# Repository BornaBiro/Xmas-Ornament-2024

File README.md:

# Xmas Ornament - 2024 update
New and updated DIY Xmas Ornament based around STM32C011 MCU.

# ! NOTE ! - PLEASE READ THIS FIRST!
Before making this project keep in mind that this PCB has an error. It's not fixed in design files, you will need it to fix it yourself!

Issues is that STM32 MCU is missing it's GND.

The fix is to scratch the soldermask and connect GND of the MCU with a piece of very thin wire.

## Board features
- Low power STM32C011F6PF MCU with 48MHz internal clock
- 12 x WS2812B-2020 RGB Adressable LEDs
- Buzzer for playing simple melodies
- Two push buttons both with wake up capability
- JST battry connector
- Li-Ion battery charger
- Low power compatable - 2uA deep sleep current
- USB-C connector for charging

I made two version of the project: one with the flex PCB (ordered from JLCPCB) and the other one with regular two layer FR4 PCB.

Flex PCB version:

FR4 PCB version:

## Board usage:
There are two buttons for controlling the ornament. At moment of connecting the battery, device is on and it's playing the melodies and also blinking the LEDs. Battery used is Li-Ion 3.7V 601220 100mAh Battery. Please check the polarity of. the battery!

- BTN1:
  - Regular button press:
    - Power on if the device is off
    - Change the melody
  - Multiple press: Noting for now. :)
  - Long press: Power down

- BTN2:
  - Regular button press: Change the LED pattern
  - Multiple press: Noting for now. :)
  - Long press: Mute/Unmute the ornament

## Requirements
- PC or a laptop
- STM32CubeIDE v1.19.0 or older (yes, older, new v2.0.0 is just bad)
  - I used STM32CubeIDE v1.19.0, Build: 25607_20250703_0907 (UTC)
- STM32C0 FW package v1.4.0
- STLink v2 (ideally with [reset mod](https://chauquest.com/index.php/article/why-your-st-link-v2-reset-doesnt-work-and-how-to-fix-it/))
- Completed PCB
- Jumper cables to connect STLink and PCB
- Soldering iron
- Li-Ion battery
- Electricity for all of that (not optional!)

## Usage
Open the project in STM32CubeIDE, build it (everything should be set-up) by pressing CTRL+B (or CMD+B on Mac) , and run the code. If, on the code run (upload) pop-up window shows up, just press Run button and the code should be uploaded to the board. If not, maybe something ins't soldered correctly, or there is a connection issue with the board or the programmer. To check that, you can use STM32CubeProgrammer - it's faster for testing programmer connection than STM32CubeIDE.

# License
All files written or created by me are using the MIT Licence and can be re-used BUT original author (me) must not be removed!
Part of the code for WS2812 LED Driver (ws2182_hsv() function code) is copied from the [Adafruit_NeoPixel library](https://github.com/adafruit/Adafruit_NeoPixel). Thanks Adafruit!

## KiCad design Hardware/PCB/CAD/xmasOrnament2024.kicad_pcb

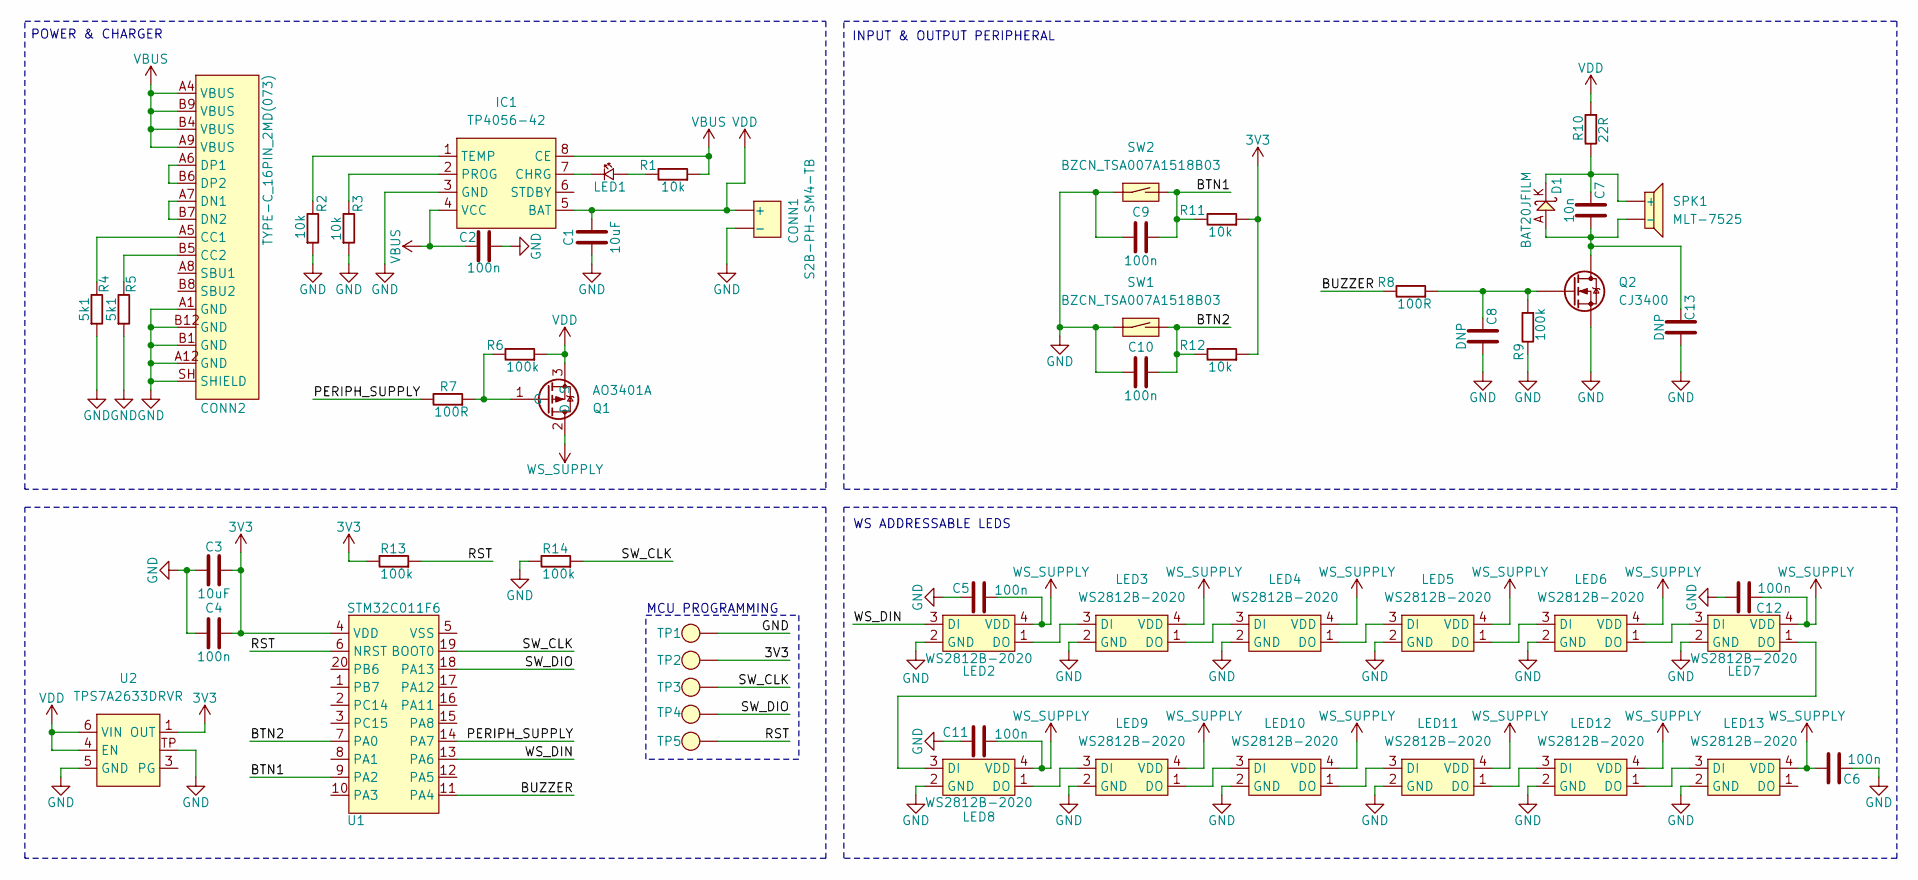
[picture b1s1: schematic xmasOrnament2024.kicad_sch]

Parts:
C1, C3: 10uF; C1206
C2, C4, C5, C6, C9, C10, C11, C12: 100n; C0603
C7: 10n; C0603
C8, C13: DNP; C0603
CONN1: S2B-PH-SM4-TB; JST_S2B-PH-SM4-TB
CONN2: TYPE-C_16PIN_2MD(073)
D1: BAT20JFILM; SOD323
IC1: TP4056-42; EMSOP
LED1: LED_0603
LED2, LED3, LED4, LED5, LED6, LED7, LED8, LED9, LED10, LED11, LED12, LED13: WS2812B-2020
Q1: AO3401A; SOT-23-3L
Q2: CJ3400; SOT-23-3L
R1, R2, R3, R11, R12: 10k; R0603
R4, R5: 5k1; R0603
R6, R9, R13, R14: 100k; R0603
R7, R8: 100R; R0603
R10: 22R; R0603
SPK1: MLT-7525; MTL-7525
SW1, SW2: BZCN_TSA007A1518B03; TSA007A1518B03
TP1, TP2, TP3, TP4, TP5: TP-1_5mm
U1: STM32C011F6; TSSOP20
U2: TPS7A2633DRVR; WSON-6

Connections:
3V3: C3.2, C4.2, R11.1, R12.1, R13.2, TP2.1 (TP), U1.4 (VDD), U2.1 (OUT)
/BTN1: C9.2, R11.2, SW2.2 (SW2), U1.9 (PA2)
/BTN2: C10.2, R12.2, SW1.2 (SW2), U1.7 (PA0)
/BUZZER: R8.2, U1.11 (PA4)
/PERIPH_SUPPLY: R7.2, U1.14 (PA7)
/RST: R13.1, TP5.1 (TP), U1.6 (NRST)
/SW_CLK: R14.1, TP3.1 (TP), U1.19 (BOOT0)
/SW_DIO: TP4.1 (TP), U1.18 (PA13)
/WS_DIN: LED2.3 (DI), U1.13 (PA6)
GND: C1.1, C2.1, C3.1, C4.1, C5.2, C6.2, C8.1, C9.1, C10.1, C11.2, C12.1, C13.1, CONN1.-, CONN2.A1 (GND), CONN2.A12 (GND), CONN2.B1 (GND), CONN2.B12 (GND), CONN2.SH (SHIELD), IC1.3 (GND), LED2.2 (GND), LED3.2 (GND), LED4.2 (GND), LED5.2 (GND), LED6.2 (GND), LED7.2 (GND), LED8.2 (GND), LED9.2 (GND), LED10.2 (GND), LED11.2 (GND), LED12.2 (GND), LED13.2 (GND), Q2.3 (S), R2.1, R3.1, R4.1, R5.1, R9.2, R14.2, SW1.1 (SW1), SW2.1 (SW1), TP1.1 (TP), U2.5 (GND), U2.TP
unnamed: C7.2, D1.K, R10.2, SPK1.+
unnamed: CONN2.A5 (CC1), R4.2
unnamed: CONN2.B5 (CC2), R5.2
unnamed: CONN2.A7 (DN1), CONN2.B7 (DN2)
unnamed: CONN2.A6 (DP1), CONN2.B6 (DP2)
unnamed: IC1.7 (CHRG), LED1.2 (K)
unnamed: IC1.2 (PROG), R3.2
unnamed: IC1.1 (TEMP), R2.2
unnamed: LED1.1 (A), R1.2
unnamed: LED2.1 (DO), LED3.3 (DI)
unnamed: LED3.1 (DO), LED4.3 (DI)
unnamed: LED4.1 (DO), LED5.3 (DI)
unnamed: LED5.1 (DO), LED6.3 (DI)
unnamed: LED6.1 (DO), LED7.3 (DI)
unnamed: LED7.1 (DO), LED8.3 (DI)
unnamed: LED8.1 (DO), LED9.3 (DI)
unnamed: LED9.1 (DO), LED10.3 (DI)
unnamed: LED10.1 (DO), LED11.3 (DI)
unnamed: LED11.1 (DO), LED12.3 (DI)
unnamed: LED12.1 (DO), LED13.3 (DI)
unnamed: Q1.1 (G), R6.2, R7.1
unnamed: C7.1, C13.2, D1.A, Q2.2 (D), SPK1.-
unnamed: C8.2, Q2.1 (G), R8.1, R9.1
VBUS: C2.2, CONN2.A4 (VBUS), CONN2.A9 (VBUS), CONN2.B4 (VBUS), CONN2.B9 (VBUS), IC1.4 (VCC), IC1.8 (CE), R1.1
VDD: C1.2, CONN1.+, IC1.5 (BAT), Q1.3 (S), R6.1, R10.1, U2.4 (EN), U2.6 (VIN)
WS_SUPPLY: C5.1, C6.1, C11.1, C12.2, LED2.4 (VDD), LED3.4 (VDD), LED4.4 (VDD), LED5.4 (VDD), LED6.4 (VDD), LED7.4 (VDD), LED8.4 (VDD), LED9.4 (VDD), LED10.4 (VDD), LED11.4 (VDD), LED12.4 (VDD), LED13.4 (VDD), Q1.2 (D)

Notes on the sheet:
INPUT & OUTPUT PERIPHERAL
POWER & CHARGER
WS ADDRESSABLE LEDS
MCU PROGRAMMING

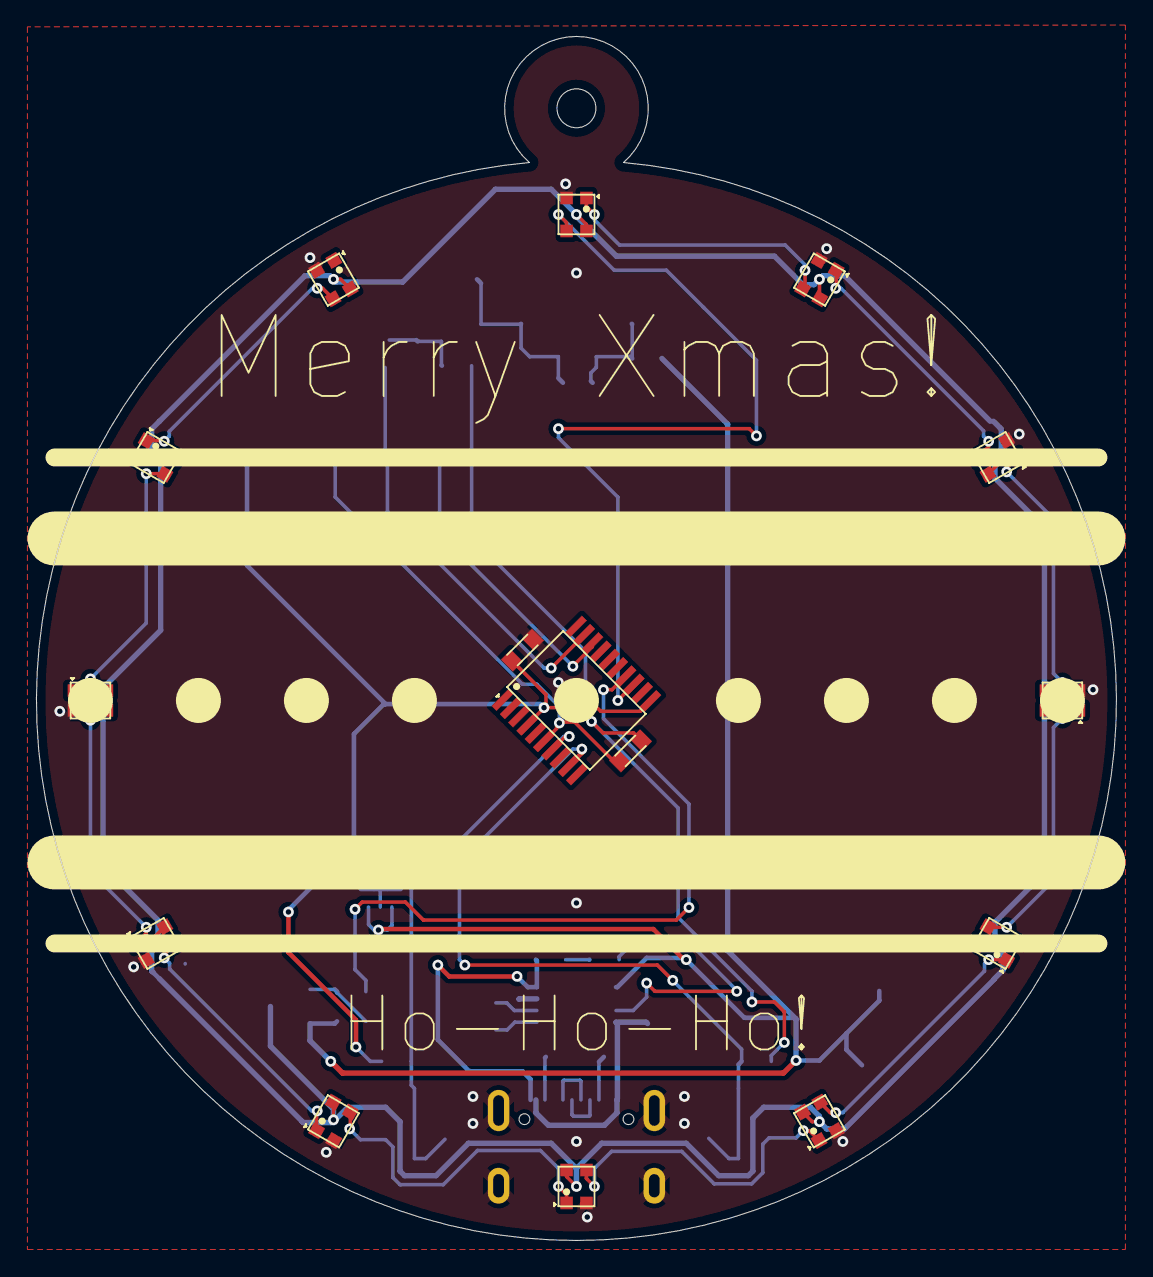
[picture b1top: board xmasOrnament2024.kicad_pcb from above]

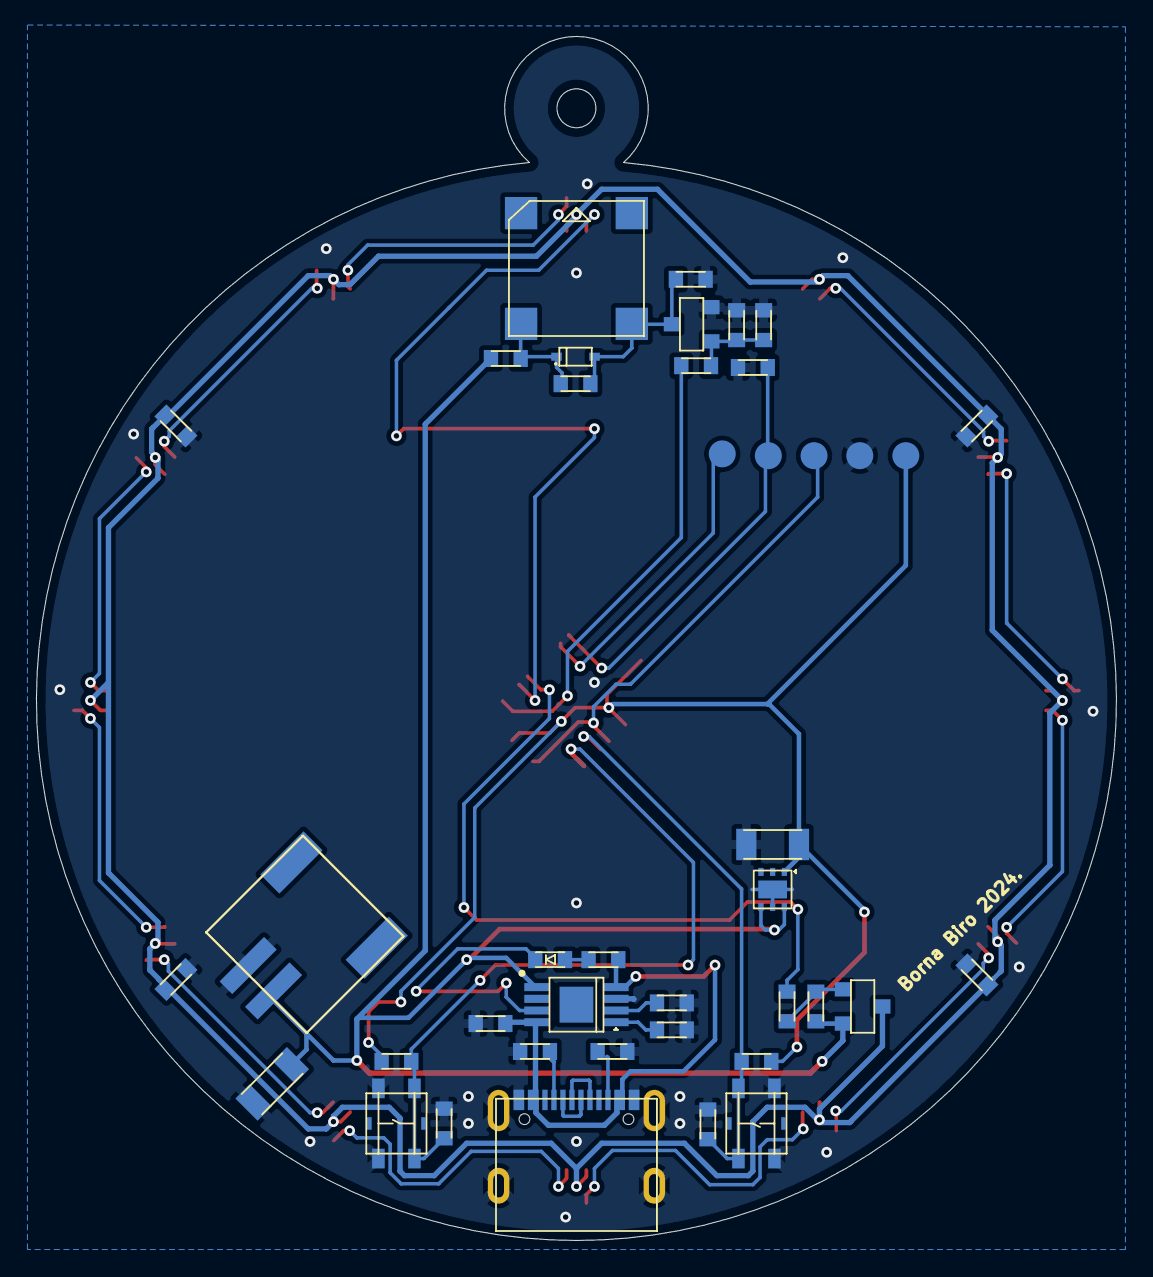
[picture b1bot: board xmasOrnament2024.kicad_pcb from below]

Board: 2 copper layers, 60.0 x 66.9 mm, 56 parts (41 on the bottom side), 36 nets.

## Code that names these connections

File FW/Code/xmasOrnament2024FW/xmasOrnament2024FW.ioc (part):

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Mcu.Name=STM32C011F(4-6)Px
Mcu.Package=TSSOP20
Mcu.UserName=STM32C011F6Px
PA0.Mode=WakeUp1
PA0.Signal=PWR_WKUP1
PA13.Mode=Serial_Wire
PA13.Signal=DEBUG_SWDIO
PA14-BOOT0.Mode=Serial_Wire
PA14-BOOT0.Signal=DEBUG_SWCLK
PA4.Signal=S_TIM14_CH1
PA6.GPIOParameters=GPIO_Speed
PA6.GPIO_Speed=GPIO_SPEED_FREQ_VERY_HIGH
PA6.Signal=S_TIM3_CH1
PA7.GPIOParameters=PinState,GPIO_PuPd,GPIO_Label,GPIO_ModeDefaultOutputPP
PA7.GPIO_Label=PERIPH
PA7.GPIO_ModeDefaultOutputPP=GPIO_MODE_OUTPUT_OD
PA7.GPIO_PuPd=GPIO_PULLUP
PA7.PinState=GPIO_PIN_SET
PA7.Signal=GPIO_Output
RCC.HSE_VALUE=8000000
RCC.SYSCLKFreq_VALUE=24000000
board=custom

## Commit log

2024-12-03 PCB added (still not finished).
2024-12-03 Fixes.
2024-12-04 Board finished.
2024-12-07 Added VREG.
2024-12-07 Removed backup files....
2024-12-10 Added gerber files.
2025-01-04 Sync - Changed typo on PCB.
2025-01-04 Added code.
2025-01-05 Added buzzer library, .ioc clean-up, added test code for wakeup, modified ws2812 library.
2025-01-09 Edited readme.
2026-01-01 Added mostly completed firmware, used on Xmas Ornament 2025.
2026-01-01 Folder and project rename.
2026-01-01 Update README to reflect project status
    Removed outdated note about project development status.
2026-01-01 Added images.
2026-01-01 README update.
2026-01-02 Updated buzzer component values.
